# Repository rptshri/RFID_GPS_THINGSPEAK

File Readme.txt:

hi there!

UID (blue tag):     36 55 C5 F7
UID (White tag):    30 B0 C7 3A 
UID (White tag):    91 9F E5 2F

a

References:

RC522:      https://www.instructables.com/id/MFRC522-RFID-Reader-Interfaced-With-NodeMCU/

RC522               NodeMCU
SS(1)               D8(gpio15)             1,2,5,6,7
SCK(2)              D5(gpio14)
MOSI(3)             D7(gpio13)
MISO(4)             D6(gpio12)
IRQ(5)              ~
GND(6)              GND
RST(7)              D1(gpio5)----(NC)
3.3v(8)             +3.3V

I2C LCD:   https://www.instructables.com/id/I2C-LCD-on-NodeMCU-V2-With-Arduino-IDE/
library link:   https://github.com/fdebrabander/Arduino-LiquidCrystal-I2C-library
LCD                 NodeMCU
VCC                 +3.3v
GND                 GND         
SDA                 D2
SCL                 D1

GPS:    https://circuitdigest.com/microcontroller-projects/interfacing-gps-with-nodemcu-esp12

GPS Pins            NodeMCU
VCC                 +3.3V
RX                  D4
TX                  D3
GND                 GND

for finding distance between two lat and long
https://andrew.hedges.name/experiments/haversine/
dlon = lon2 - lon1 
dlat = lat2 - lat1 
a = (sin(dlat/2))^2 + cos(lat1) * cos(lat2) * (sin(dlon/2))^2 
c = 2 * atan2( sqrt(a), sqrt(1-a) ) 
d = R * c (where R is the radius of the Earth)

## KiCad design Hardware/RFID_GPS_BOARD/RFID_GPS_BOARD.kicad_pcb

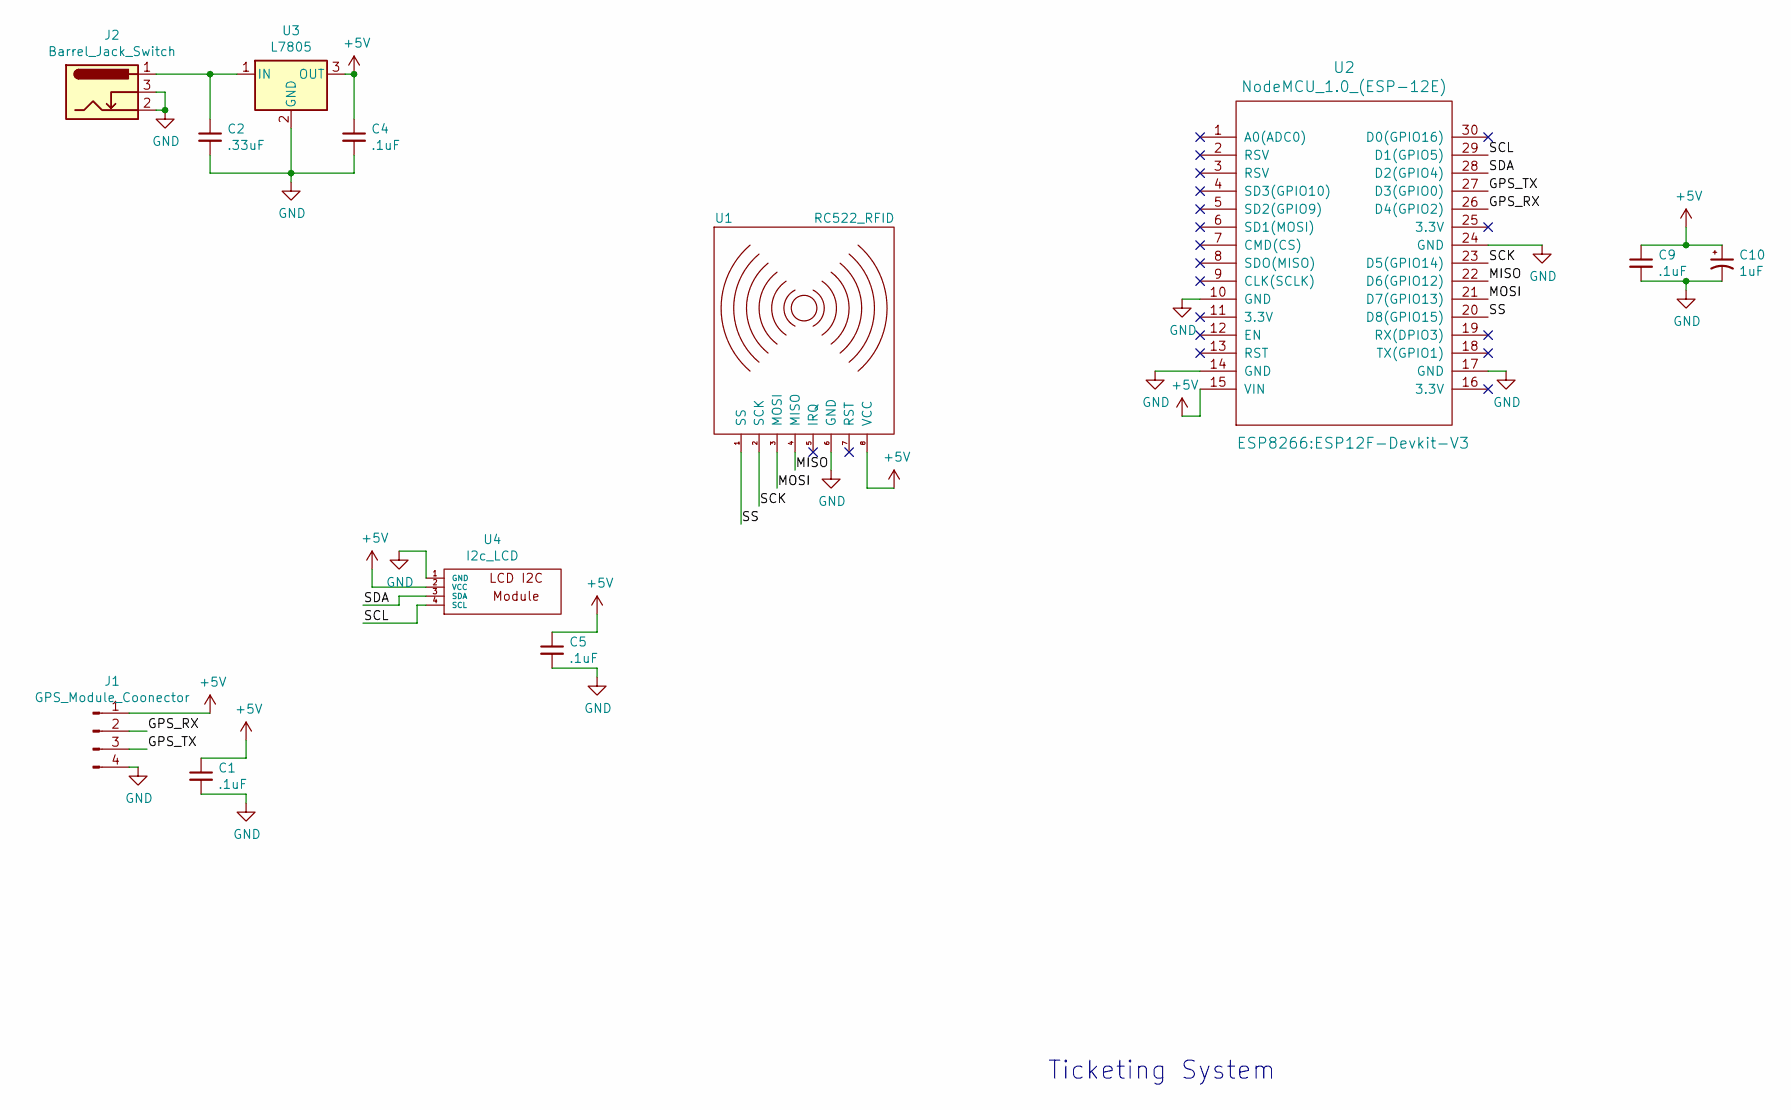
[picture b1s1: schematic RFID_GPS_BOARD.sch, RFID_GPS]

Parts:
C1, C4, C5, C9: .1uF; C_Disc_D3.0mm_W1.6mm_P2.50mm
C2: .33uF; C_Disc_D3.0mm_W1.6mm_P2.50mm
C10: 1uF; CP_Radial_D5.0mm_P2.50mm
J1: GPS_Module_Coonector; PinHeader_1x04_P2.54mm_Vertical
J2: Barrel_Jack_Switch
U1: RC522_RFID; PinHeader_1x08_P2.54mm_Vertical
U2: NodeMCU_1.0_(ESP-12E); ESP12F-Devkit-V3
U3: L7805; TO-220-3_Vertical
U4: I2c_LCD; LCD_I2C

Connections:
+5V: C1.1, C4.1, C5.1, C9.1, C10.1, J1.1, U1.8 (VCC), U2.15 (VIN), U3.3 (OUT), U4.2 (VCC)
/GPS_RX: J1.2, U2.26 (D4(GPIO2))
/GPS_TX: J1.3, U2.27 (D3(GPIO0))
/MISO: U1.4 (MISO), U2.22 (D6(GPIO12))
/MOSI: U1.3 (MOSI), U2.21 (D7(GPIO13))
/SCK: U1.2 (SCK), U2.23 (D5(GPIO14))
/SCL: U2.29 (D1(GPIO5)), U4.4 (SCL)
/SDA: U2.28 (D2(GPIO4)), U4.3 (SDA)
/SS: U1.1 (SS), U2.20 (D8(GPIO15))
GND: C1.2, C2.2, C4.2, C5.2, C9.2, C10.2, J1.4, J2.2, J2.3, U1.6 (GND), U2.10 (GND), U2.14 (GND), U2.17 (GND), U2.24 (GND), U3.2 (GND), U4.1 (GND)
unnamed: C2.1, J2.1, U3.1 (IN)

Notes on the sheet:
Ticketing System

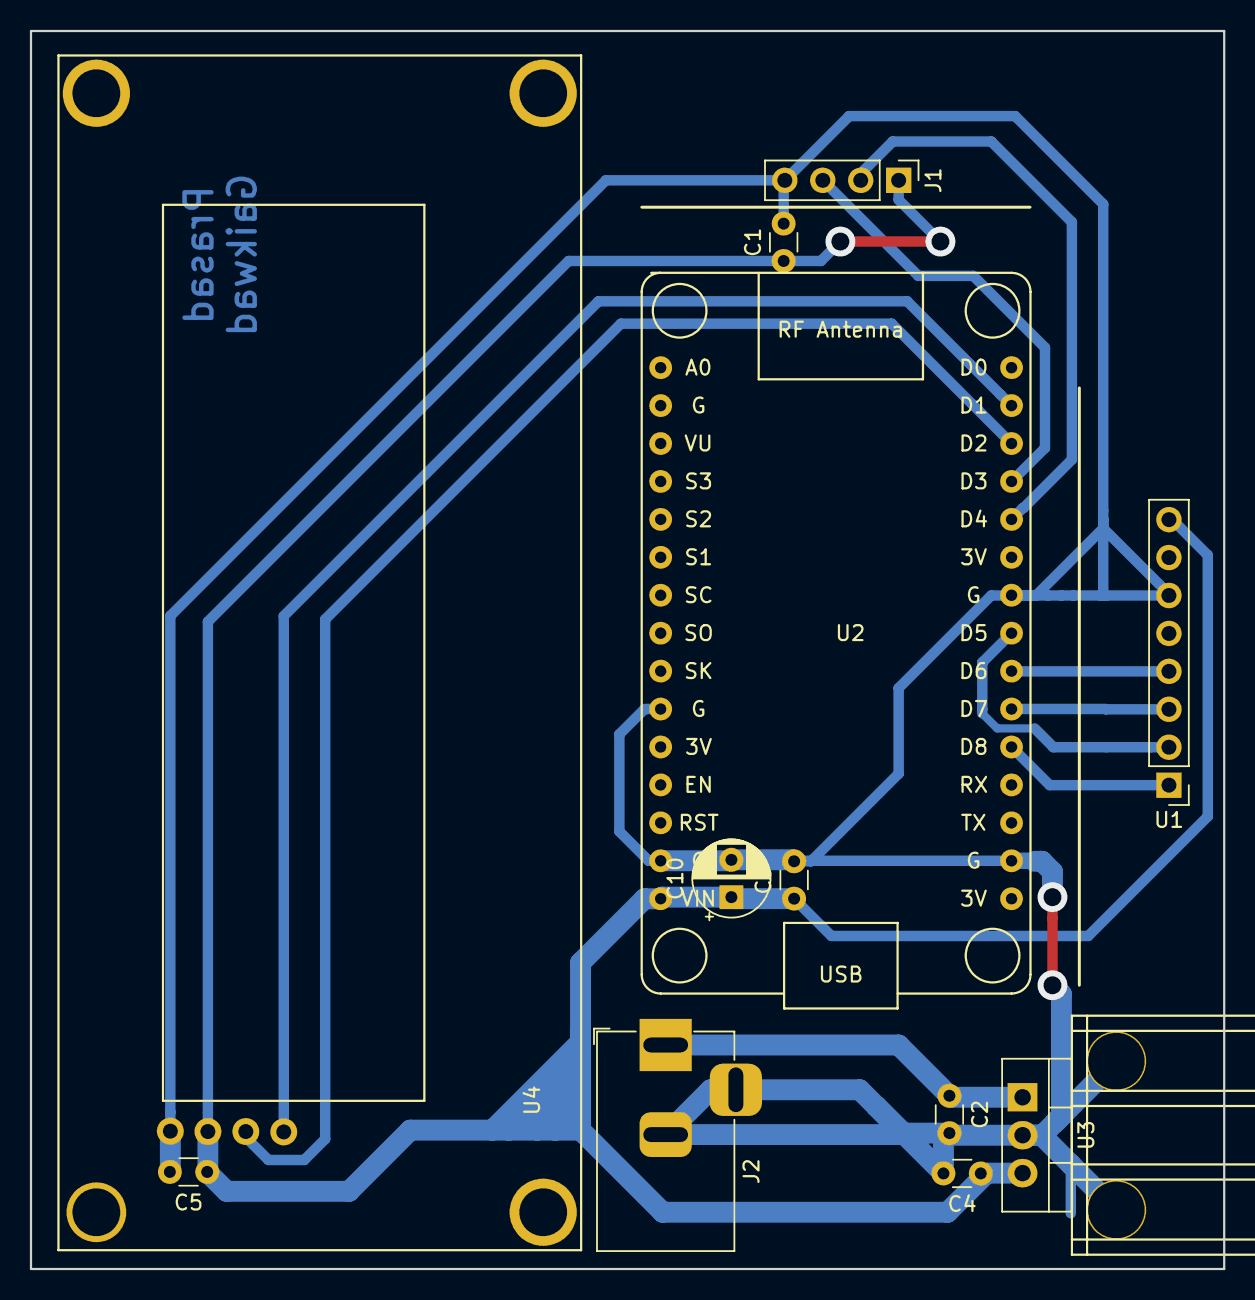
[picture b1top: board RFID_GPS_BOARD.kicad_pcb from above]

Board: 2 copper layers, 79.9 x 82.9 mm, 12 parts (0 on the bottom side), 11 nets.

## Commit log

2019-05-01 first Update
2019-05-01 RC522 test Complete
2019-06-02 working location code
2019-06-05 almost done
2019-06-05 completed project final
2019-06-05 update report and documentation
2019-06-05 create cloud vs terminal
2019-06-05 libararies added
2019-06-05 upadtesaad
2019-06-05 added
2019-08-11 final update
2020-05-25 [ImgBot] Optimize images
    *Total -- 836.82kb -> 692.12kb (17.29%)
    /Hardware/RFID_GPS_BOARD/RFID_GPS_BOARD-Edge.Cuts.svg -- 1.02kb -> 0.52kb (49%)
    /Hardware/RFID_GPS_BOARD/RFID_GPS_BOARD-B.Cu.svg -- 72.99kb -> 48.75kb (33.21%)
    /libraries/MFRC522/doc/fritzing/RFID-RC522-v3.png -- 17.37kb -> 11.71kb (32.58%)
    /libraries/MFRC522/doc/fritzing/RFID-RC522-v2.png -- 29.37kb -> 22.52kb (23.31%)
    /libraries/MFRC522/doc/fritzing/Arduino-Uno-r3-with-RFID-RC522.png -- 282.35kb -> 232.35kb (17.71%)
